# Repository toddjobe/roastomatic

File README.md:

# roastomatic

Coffee Roasting using ESP32

I had a 4$ hot air popcorn popper that I used in 2005 for roasting coffee.  My roasting was atrocious.  I waited 20 years and people across the internets got a lot a smarter about roasting coffee at home.  So, I thought if I added bit more smarts to my hot air popcorn popper, i *might* make a decent roast.

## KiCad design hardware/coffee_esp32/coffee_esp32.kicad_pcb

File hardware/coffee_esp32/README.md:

# coffee_esp32 Design

The footprints and symbols are downloaded from https://www.snapeda.com/.  See LICENSE

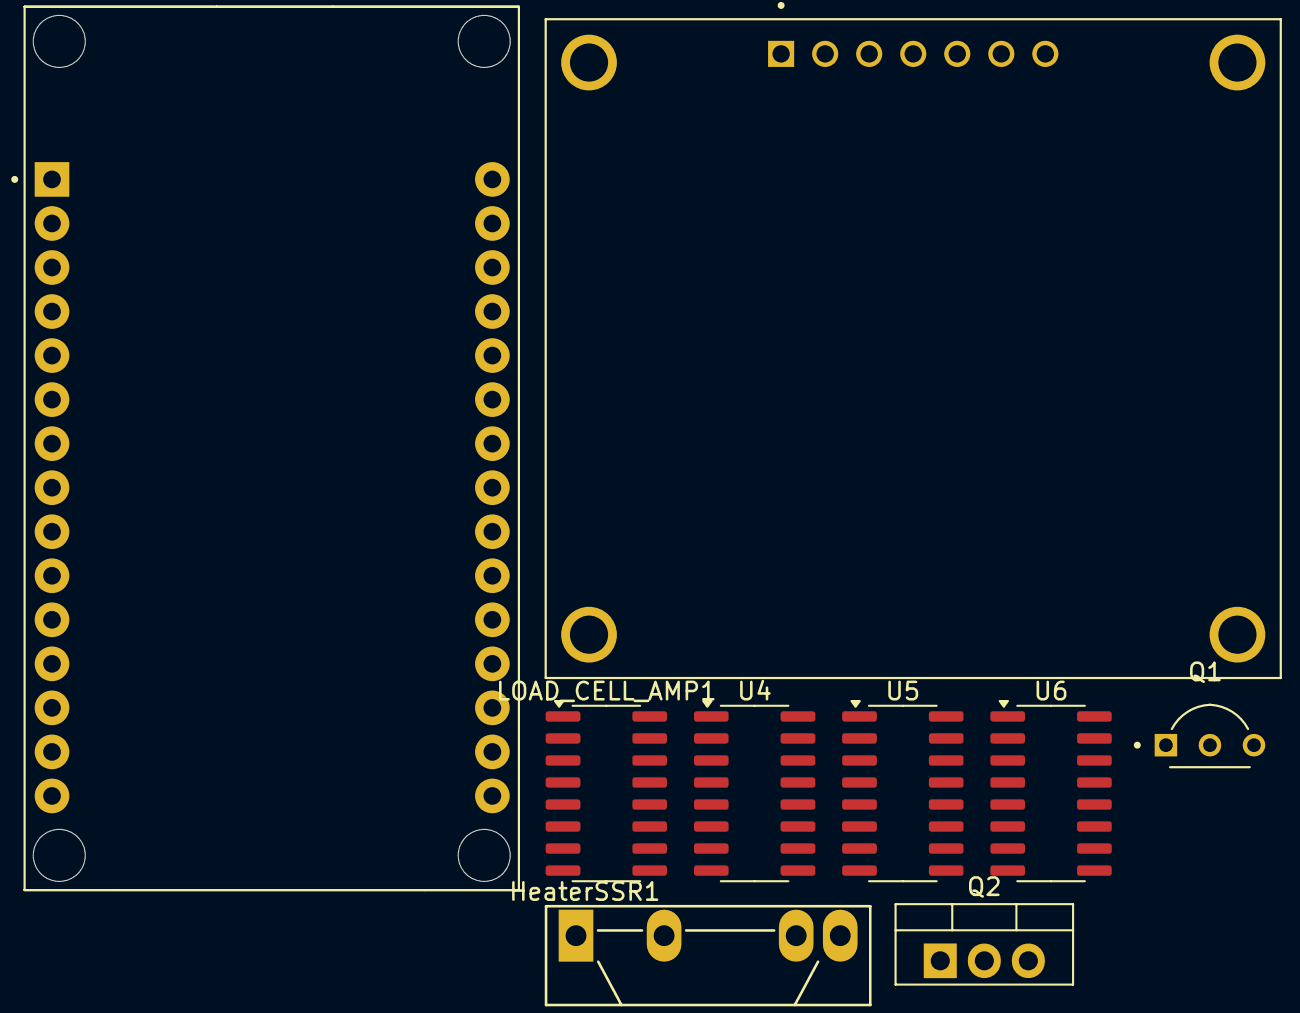
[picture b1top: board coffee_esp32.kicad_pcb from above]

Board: 2 copper layers, 9 parts (0 on the bottom side), 4 nets, no tracks yet.

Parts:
DS1: AOM12864A0-1.54WW-ANO; LCD_AOM12864A0-1.54WW-ANO
HeaterSSR1: SSR-40 DA; SIP4_Sharp-SSR_P7.62mm_Straight
LOAD_CELL_AMP1: HX711; SOP-16_3.9x9.9mm_P1.27mm
Q1: 2N2222A; TO92254P470H750-3
Q2: TIP120; TO-220-3_Vertical
U1: ESP32-DEVKIT-V1; MODULE_ESP32_DEVKIT_V1
U4, U5, U6: HX711; SOP-16_3.9x9.9mm_P1.27mm

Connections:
+3.3V: DS1.2 (VDD), LOAD_CELL_AMP1.1 (VSUP), U1.1 (3V3)
/Load Cell DOUT: LOAD_CELL_AMP1.12 (DOUT), U1.19 (D34)
/Load Cell SCK: LOAD_CELL_AMP1.11 (PD_SCK), U1.20 (D35)
GND: DS1.1 (GND), HeaterSSR1.4, LOAD_CELL_AMP1.5 (AGND), Q2.3 (E), U1.2 (GND), U1.29 (GND)

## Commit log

2025-02-15 First README.md update
2025-02-15 Created initial folder structure.
2025-02-15 Added KiCad and Python gitignore templates
2025-02-15 Added spellings of gitignore to dictionary
2025-02-15 added coffee_esp32 with hardware
2025-02-15 made platformio project and added code
2025-02-15 added thermocouple testing code
2025-02-16 Added heater pwm
2025-02-19 PWM of fan added and tested,
2025-02-22 test load cell works
2025-02-22 formatting
2025-02-22 upgrade to kicad 9
2025-02-22 load cell testing tares and calibrates
2025-02-23 turn everyone on by default
2025-02-23 added serial sink in python
2025-03-01 last commit on #18
2025-03-01 ignore python outputs
2025-03-01 added main copyright
2025-03-02 First foray into analysis
2025-03-08 First Roast analyzed draft
2025-05-05 refactor
2025-05-05 removed absolute paths
2025-05-15 started refactor of HardwareTimer
2025-06-01 All functions seem to work but filter is too slow
